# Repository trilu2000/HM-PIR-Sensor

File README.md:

# HM-PIR-Sensor

dieses Repo beinhaltet alle Infos und Dateien die es zum Nachbau eines Homematic kompatiblen PIR Sensors braucht.

Der PIR-Sensor ist streng genommen ein selbstgedrucktes Gehäuse und eine Zusatzplatine für den HMSensor (https://asksinpp.de/Projekte/psi/HMSensor/). 

Die Software ist eine Abwandlung vom HM-SEC-MDIR Sketch aus den Beispielen der Asksin Library. 

Ein wesentliches Highlight des PIR Sensors ist der verbaute Helligkeitssensor - Ich nutze den OPT3001 und wandle den gemessenen LUX Wert in einen HM Helligkeitswert.
Die HM Helligkeitswerte habe ich in einer Meßreihe mit einem selbstgebautem LUX-Sensor und einem HomeMatic MDIR-WM-55 ermittelt.
Das Ergebnis findet ihr in der Exceltabelle im GIT-Hub (https://github.com/trilu2000/HM-PIR-Sensor/blob/main/DOCU/PIR-Addon.xlsm)

## Benötigtes Material

HM-Sensor Platine, bis auf die LED und Vorwiderstände, bestückt

PIR Addon Platine, bis auf den AD5247, bestückt

Die Gehäuse Files gedruckt - ich habe sie aus PLA mit 25% infill gedruckt

PIR Optische Fresnel-Linse 23.3*23.3*14,7mm (https://de.aliexpress.com/item/1005001664621201.html)

Batterie-Federn (https://de.aliexpress.com/item/4001112851052.html)

## Forum

https://homematic-forum.de/forum/viewtopic.php?f=76&t=68096

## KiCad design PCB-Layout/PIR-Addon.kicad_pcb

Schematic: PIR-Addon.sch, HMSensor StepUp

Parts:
A1: AM612
C1: 100n; C_0805_2012Metric_Pad1.15x1.40mm_HandSolder
D1: LED_Dual_ACA; LED_D3.0mm-3
IC1: OPT3001DNPR; SON65P200X200X65-7N-D; Manufacturer_Part_Number OPT3001DNPR; Mouser Part Number 595-OPT3001DNPR
IC2: AD5247BKSZ10-RL7; SOT65P210X110-6N; Manufacturer_Part_Number AD5247BKSZ10-RL7; Mouser Part Number 584-AD5247BKSZ10-R7
JP1: Jumper_2_Bridged; SolderJumper-2_P1.3mm_Open_Pad1.0x1.5mm
P1, P6: Contacts; Pin_Header_Straight_1x04_Pitch2.54mm
P2: Contacts; Pin_Header_Straight_1x06_Pitch2.54mm
R2, R3: 1k5; R_0805_2012Metric_Pad1.15x1.40mm_HandSolder
R4, R8: 1M; R_0805_2012Metric_Pad1.15x1.40mm_HandSolder
R5: 56k; R_0805_2012Metric_Pad1.15x1.40mm_HandSolder
R6, R7: 10k; R_0805_2012Metric_Pad1.15x1.40mm_HandSolder

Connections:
/A0: P1.3, R3.1
/A1: P1.4, R2.1
/A2: A1.5, P2.1
/A3: P2.2
/A4: IC1.6, IC2.4, P2.3, R7.2
/A5: IC1.4, IC2.3, P2.4, R6.2
/B1: P6.3
/D3: P2.5
/D6: P2.6
/D7: P6.4
/SENS: A1.1, IC2.5, R4.1, R5.2
/Vin: JP1.1, P1.1
GND: A1.3, A1.6, C1.2, D1.2, IC1.2, IC1.3, IC1.7, IC2.2, P1.2, P6.1, R5.1
unnamed: A1.2, R8.1
unnamed: D1.1, R2.2
unnamed: D1.3, R3.2
VCC: A1.4, C1.1, IC1.1, IC2.1, JP1.2, P6.2, R4.2, R6.1, R7.1, R8.2

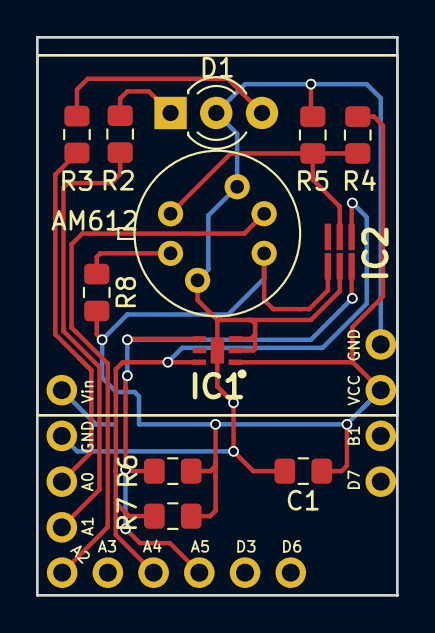
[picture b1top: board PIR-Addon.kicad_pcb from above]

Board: 2 copper layers, 20.0 x 31.0 mm, 16 parts (1 on the bottom side), 12 nets.

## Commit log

2021-06-05 added pictures
2021-06-06 update pictures
2021-06-06 removed jpg
2021-06-06 folder renamed
2021-07-08 update with Wallmount
2021-12-09 case update
